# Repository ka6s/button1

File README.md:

Button board for the Raspberry PI PiHPSDR control software

There are 6 KY-040 rotary encoders mounted on a board that can be
connected directly to the Raspberry PI 3 board.  The bigger 20x2
connector is used to connect all of the useful GPIOs to the rotary 
encoders on this board - or on an second peripheral board that has 
the remaining buttons and the big 600 ppr encoder used for tuning.

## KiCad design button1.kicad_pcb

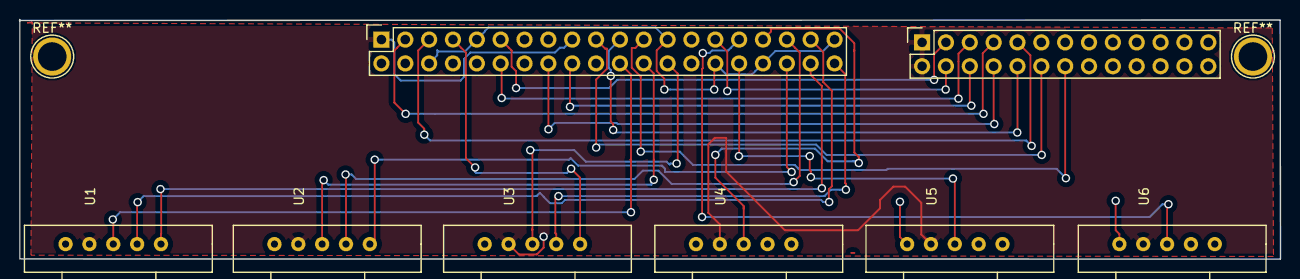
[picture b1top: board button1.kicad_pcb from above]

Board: 2 copper layers, 134.3 x 25.5 mm, 8 parts (0 on the bottom side), 24 nets.

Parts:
P1: CONN_02X20; Socket_Strip_Straight_2x20
P2: CONN_02X13; Socket_Strip_Straight_2x13
U1, U2, U3, U4, U5, U6: KY-040

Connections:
+3V3: P1.1, P1.17, P2.1, P2.2, U1.4, U2.4, U3.4, U4.4, U5.4, U6.4
/GPIO2: P1.3, P2.7
/GPIO3: P1.5, P2.9
/GPIO4: P1.7, U3.1
/GPIO5: P1.29, P2.4
/GPIO6: P1.31, U6.3
/GPIO7: P1.26, U3.3
/GPIO8: P1.24, U2.3
/GPIO9: P1.21, P2.10
/GPIO10: P1.19, P2.12
/GPIO11: P1.23, P2.14
/GPIO12: P1.32, U5.3
/GPIO13: P1.33, U4.3
/GPIO16: P1.36, U2.1
/GPIO17: P1.11, P2.3
/GPIO18: P1.12, P2.5
/GPIO19: P1.35, U2.2
/GPIO20: P1.38, U1.1
/GPIO21: P1.40, U3.2
/GPIO23: P1.16, P2.8
/GPIO24: P1.18, P2.6
/GPIO25: P1.22, U1.3
/GPIO26: P1.37, U1.2
GND: P1.6, P1.9, P1.14, P1.20, P1.25, P1.30, P1.34, P1.39, P2.25, P2.26, U1.5, U2.5, U3.5, U4.5, U5.5, U6.5
